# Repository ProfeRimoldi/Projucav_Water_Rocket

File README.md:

# 🚀 ProJuCAv – Water Rocket with Avionics

## 📡 Descripción del Proyecto

**ProJuCAv (Proyecto de Cohete de Agua con Aviónica)** es una iniciativa educativa basada en metodologías STEM que integra **física, electrónica, programación y diseño mecánico** en el desarrollo de un sistema aeroespacial a escala.

El proyecto propone el diseño, construcción y validación de un **cohete de agua instrumentado**, capaz de medir, registrar y transmitir datos de vuelo en tiempo real.

📘 Inspirado en programas aeroespaciales reales, el enfoque busca trasladar conceptos de ingeniería de alta complejidad a un entorno educativo práctico.

---

## 🎯 Objetivos

* Comprender los principios físicos de la **propulsión por reacción** (Tercera Ley de Newton) 
* Diseñar y construir un vehículo de lanzamiento funcional
* Desarrollar un sistema de **aviónica embarcada**
* Implementar una **estación terrena de telemetría**
* Analizar datos reales de vuelo
* Fomentar el trabajo colaborativo y multidisciplinario

📊 Según la planificación del proyecto, se estructura en etapas progresivas de diseño, integración y validación.

---

## 🧩 Arquitectura del Sistema

El sistema se divide en tres subsistemas principales:

### 🔧 Estructura (Mecánica)

* Botellas PET (fuselaje)
* Aletas aerodinámicas
* Sistema de presurización
* Plataforma de lanzamiento

### ⚡ Aviónica (Electrónica)

* Microcontrolador (ESP32)
* Sensores:

  * Altímetro barométrico (BMP280)
  * Acelerómetro (MPU6050)
* Sistema de almacenamiento local (microSD)
* Módulo de comunicación (LoRa)
* Sistema de alimentación (LiPo + regulación)

📌 La arquitectura electrónica completa se describe en 

---

### 📡 Estación Terrena

* Receptor de telemetría
* Computadora de procesamiento
* Software de visualización en tiempo real

---

## 📡 Telemetría y Adquisición de Datos

El sistema permite:

* Medición de **altura, aceleración y velocidad**
* Registro de datos en tiempo real y post-vuelo
* Transmisión inalámbrica a estación terrena

---

## 🚀 Propulsión

El cohete utiliza propulsión hidráulica basada en:

* Aire comprimido (energía potencial)
* Agua (masa de reacción)

✔ Basado en la **Tercera Ley de Newton**
✔ Expulsión de masa → generación de empuje

---

## 🪂 Sistema de Recuperación

El sistema de recuperación es crítico para la misión:

* Detección de apogeo mediante aviónica.
* Despliegue de paracaídas en apogeo.

---

## 🧪 Etapas del Proyecto

Según la planificación general:

1. **Diseño y fundamentos**
2. **Construcción del cohete**
3. **Integración de aviónica**
4. **Telemetría y pruebas**
5. **Lanzamiento final**

---

## 🛰️ Aviónica – Enfoque del Desarrollo

La aviónica evoluciona en niveles:

* 🔹 Nivel básico: sensores esenciales
* 🔹 Nivel intermedio: registro de datos (caja negra)
* 🔹 Nivel avanzado: telemetría en tiempo real
* 🔹 Nivel completo: sistema autónomo

---

## ⚙️ Tecnologías Utilizadas

* ESP32 (control principal)
* Sensores MEMS
* Comunicación inalámbrica

---

## 📁 Estructura del Repositorio

```bash
Projucav_Water_Rocket/
│
├── firmware/        # Código del sistema embebido
├── hardware/        # Diseño electrónico y PCB
├── docs/            # Documentación técnica y académica
└── README.md        # Descripción general del proyecto
```

---

## 👨‍🏫 Contexto Educativo

* Institución: Instituto Juan XXIII
* Modalidad: Aprendizaje basado en proyectos (PBL)
* Duración: ~5 meses
* Trabajo en equipos multidisciplinarios

---

## 🎓 Enfoque del Proyecto

Este proyecto busca replicar, a escala educativa, un sistema aeroespacial real, integrando:

* Ingeniería electrónica
* Física aplicada
* Programación embebida
* Diseño mecánico
* Análisis de datos

---

## 🚀 Autores / Desarrollo

**Diego Otero**; **Damián Rimoldi**
* Ingeniería en Electrónica – Docentes – Investigadores

Quien escribe:
Responsable del desarrollo de la **aviónica y sistema electrónico** del proyecto.

---

## 📌 Estado del Proyecto

🟡 En desarrollo
🔧 Etapa: Diseño e integración de sistemas

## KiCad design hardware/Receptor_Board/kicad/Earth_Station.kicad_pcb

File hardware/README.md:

Hardware Documentation.

Conexión de sensores: Usar firmware para detectar direcciones (ya cargado)
-MPU6050 (gyro) en bus I2C: DIR: 0x68
-BMP280 (Atmosferic Pressure) en bus I2C: Dir: 0x77

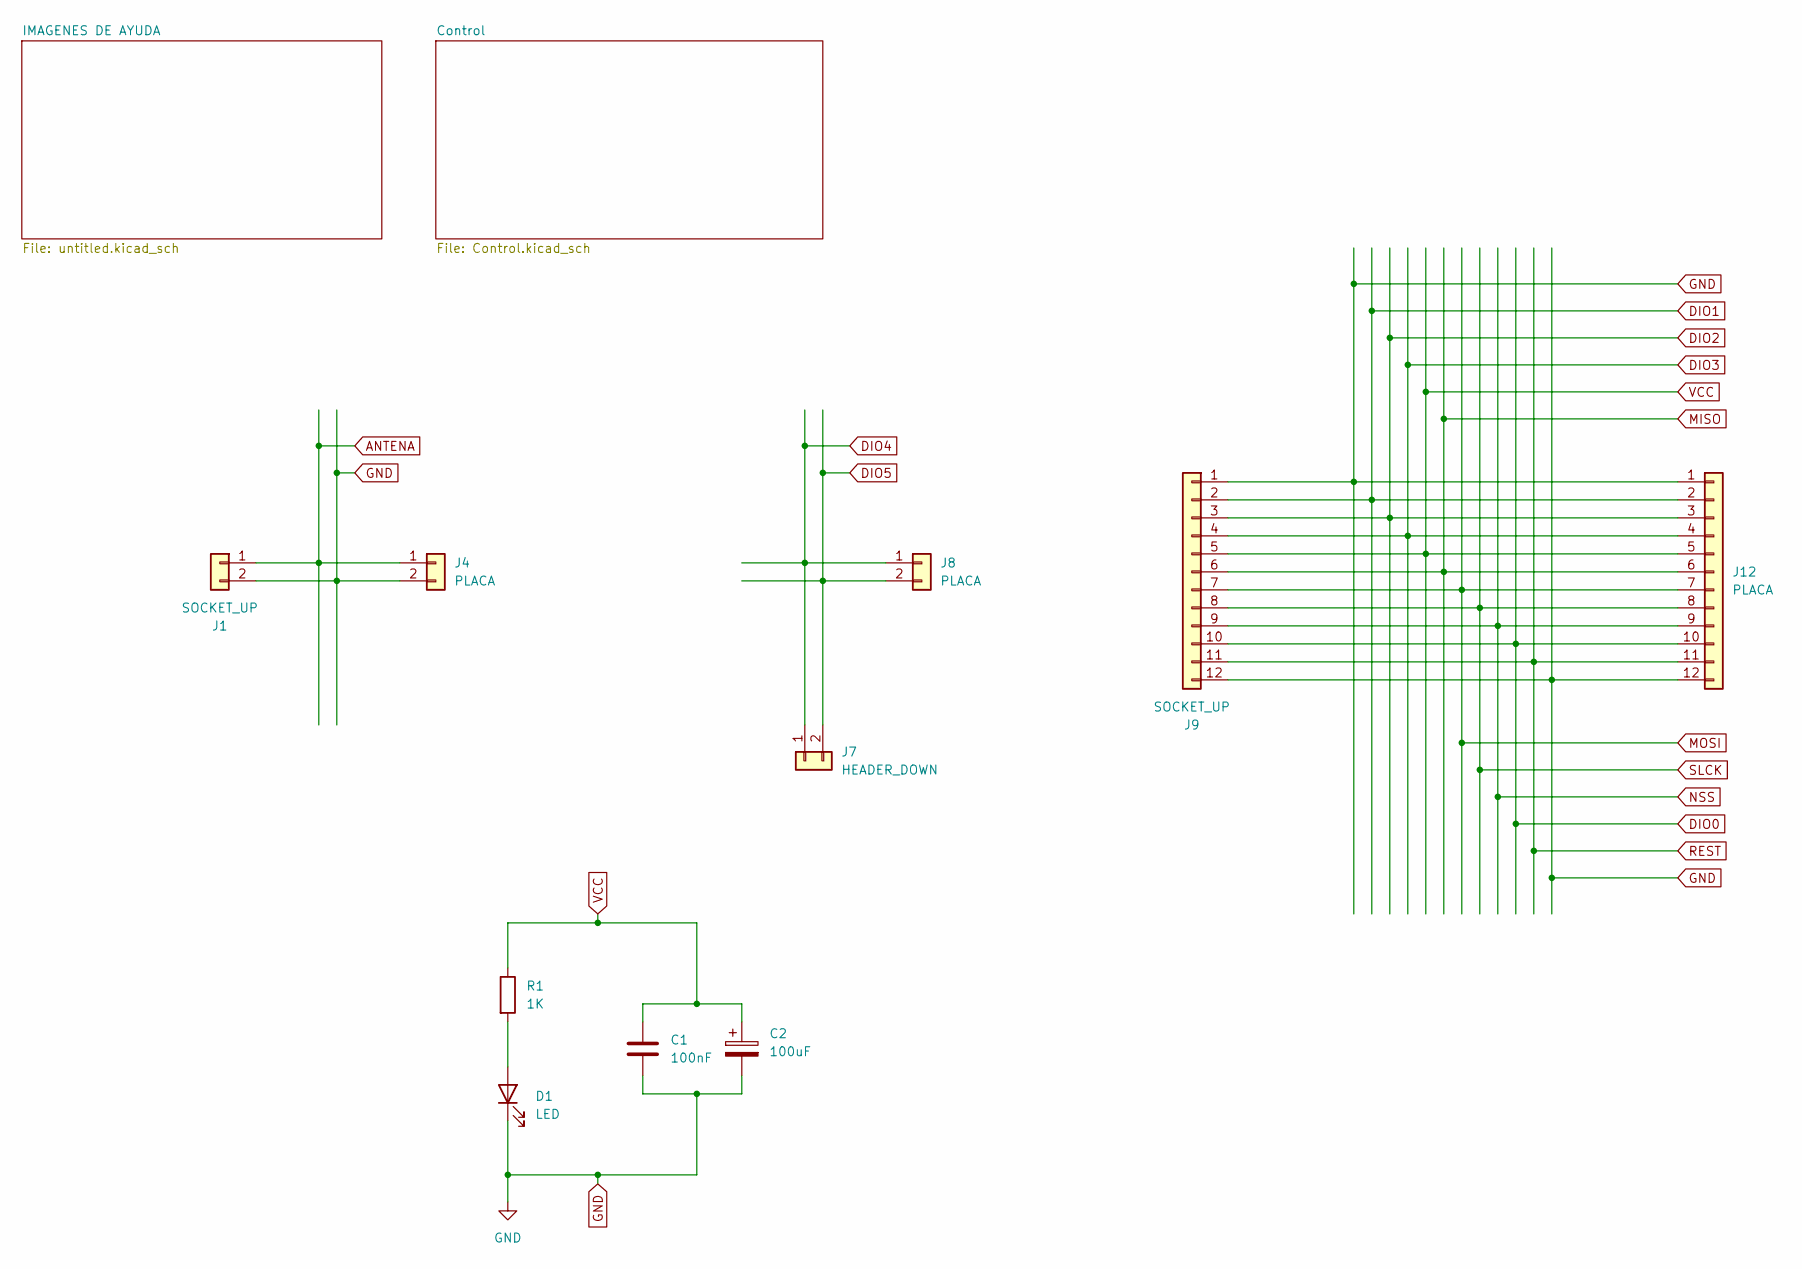
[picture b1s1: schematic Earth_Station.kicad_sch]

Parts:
C1: 100nF; C_0805_2012Metric
C2: 100uF; CP_Elec_5x3
D1: LED; LED_0805_2012Metric_Pad1.15x1.40mm_HandSolder
J1: SOCKET_UP; PinSocket_1x02_P2.54mm_Vertical
J4, J8: PLACA; PinHeader_1x02_P1.27mm_Vertical
J7: HEADER_DOWN; PinHeader_1x02_P2.54mm_Vertical
J9: SOCKET_UP; PinSocket_1x12_P2.54mm_Vertical
J12: PLACA; PinHeader_1x12_P1.27mm_Vertical
R1: 1K; R_0805_2012Metric_Pad1.20x1.40mm_HandSolder

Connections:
ANTENA: J1.1, J4.1
DIO0: J9.10, J12.10; also elsewhere on the board
DIO1: J9.2, J12.2
DIO2: J9.3, J12.3
DIO3: J9.4, J12.4
DIO4: J7.1, J8.1
DIO5: J7.2, J8.2
GND: C1.2, C2.2, D1.1 (K), J1.2, J4.2, J9.1, J9.12, J12.1, J12.12; also elsewhere on the board
MISO: J9.6, J12.6; also elsewhere on the board
MOSI: J9.7, J12.7; also elsewhere on the board
NSS: J9.9, J12.9; also elsewhere on the board
unnamed: D1.2 (A), R1.2
REST: J9.11, J12.11
SLCK: J9.8, J12.8; also elsewhere on the board
VCC: C1.1, C2.1, J9.5, J12.5, R1.1; also elsewhere on the board

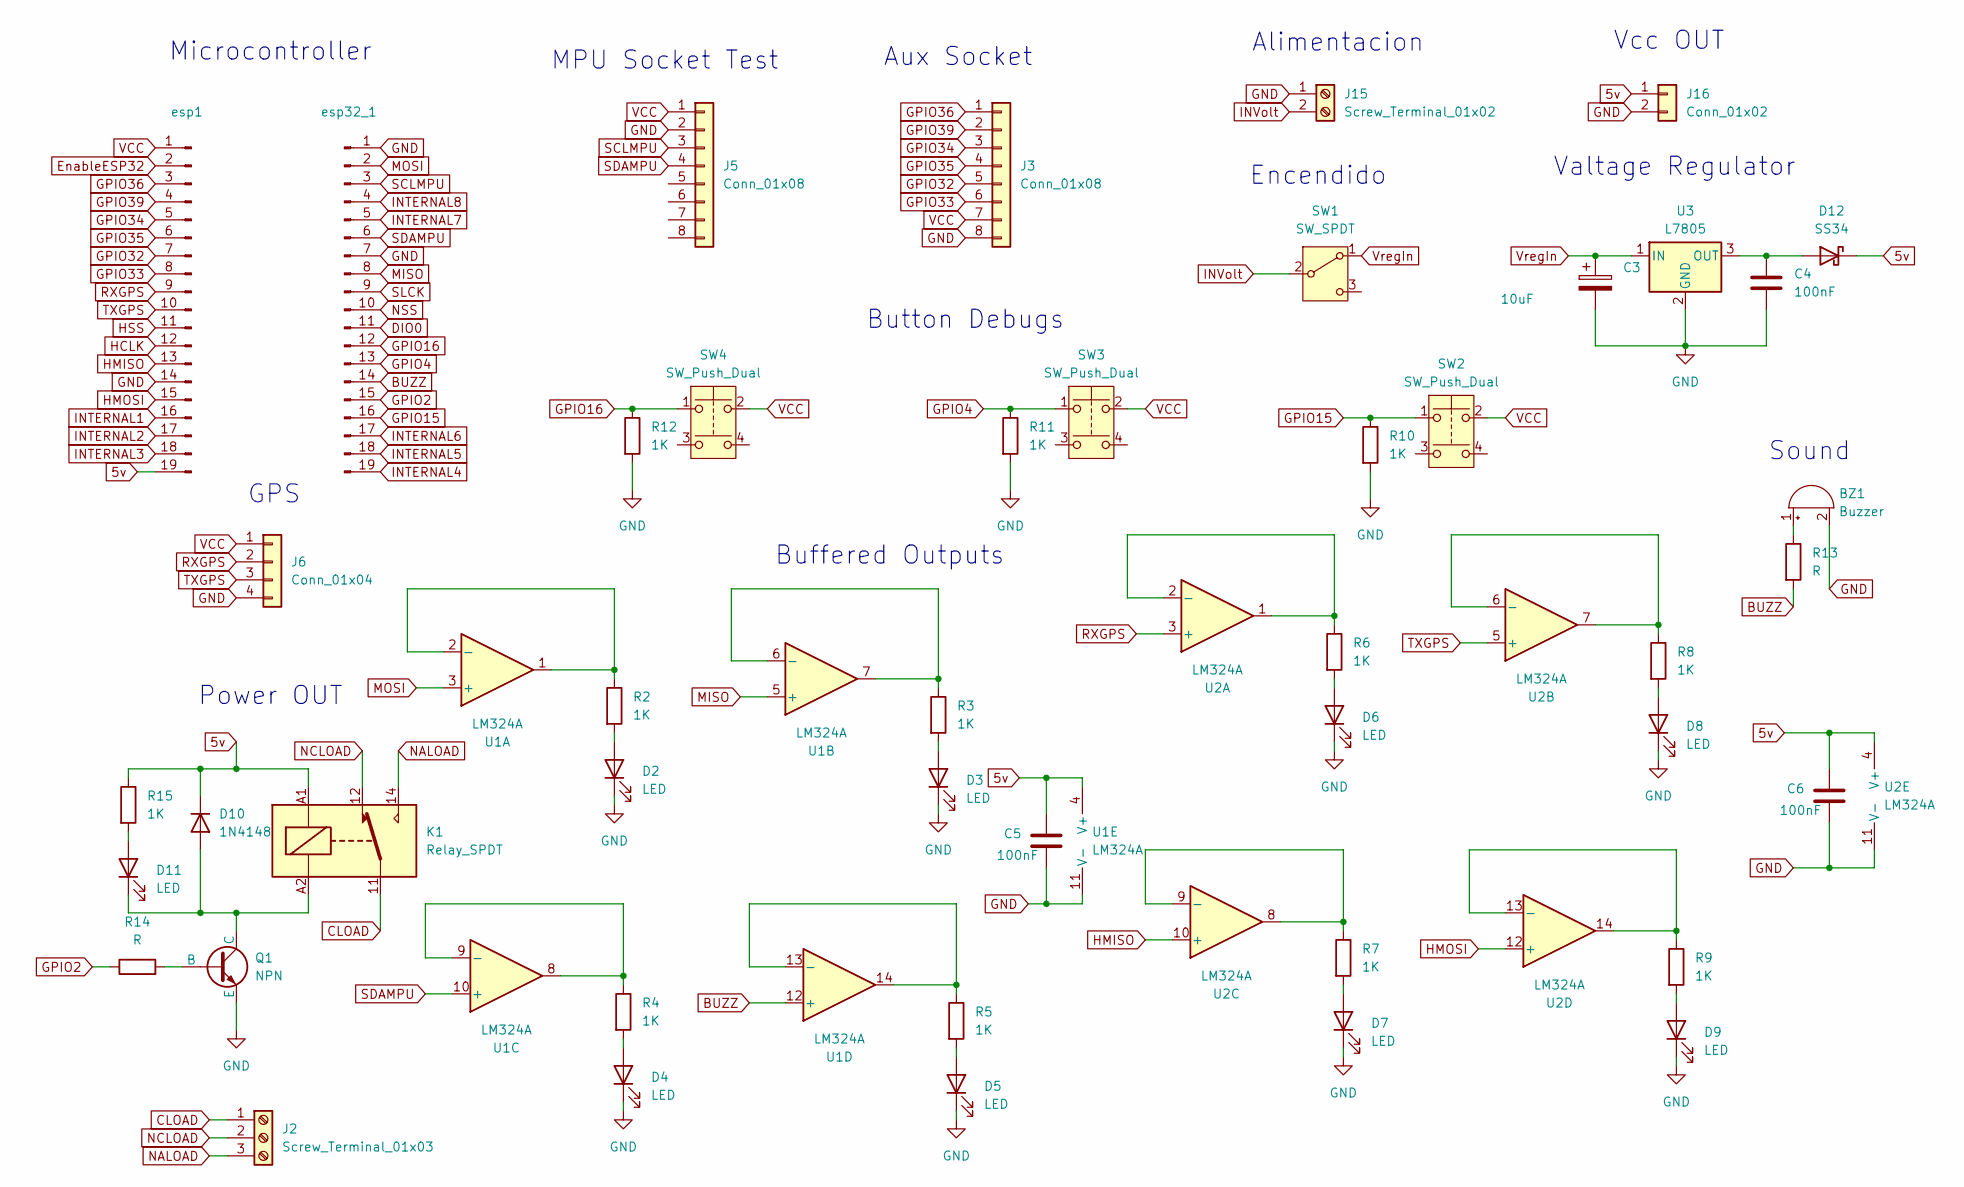
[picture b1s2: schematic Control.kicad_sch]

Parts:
BZ1: Buzzer; Buzzer_TDK_PS1240P02BT_D12.2mm_H6.5mm
C3: 10uF; CP_Elec_5x3.9
C4, C5, C6: 100nF; C_0805_2012Metric
D2, D3, D4, D5, D6, D7, D8, D9, D11: LED; LED_0805_2012Metric_Pad1.15x1.40mm_HandSolder
D10: 1N4148; D_DO-35_SOD27_P7.62mm_Horizontal
D12: SS34; D_3220_8050Metric_Pad2.65x5.15mm_HandSolder
J2: Screw_Terminal_01x03; TerminalBlock_bornier-3_P5.08mm
J3, J5: Conn_01x08; PinSocket_1x08_P2.54mm_Vertical
J6: Conn_01x04; PinSocket_1x04_P2.54mm_Vertical
J15: Screw_Terminal_01x02; TerminalBlock_bornier-2_P5.08mm
J16: Conn_01x02; PinSocket_1x02_P2.54mm_Vertical
K1: Relay_SPDT; Relay_SPDT_Finder_36.11
Q1: NPN; TO-92L_Inline
R2, R3, R4, R5, R6, R7, R8, R9, R10, R11, R12, R15: 1K; R_0805_2012Metric_Pad1.20x1.40mm_HandSolder
R13: R; R_0805_2012Metric_Pad1.20x1.40mm_HandSolder
R14: R; R_0805_2012Metric
SW1: SW_SPDT; SW_Slide_SPDT_Straight_CK_OS102011MS2Q
SW2, SW3, SW4: SW_Push_Dual; SW_Push_1P1T_NO_Vertical_Wuerth_434133025816
U1, U2: LM324A; SOIC-14_3.9x8.7mm_P1.27mm
U3: L7805; TO-263-2
esp1, esp32_1: Conn_01x19_Pin; PinSocket_1x19_P2.54mm_Vertical

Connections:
5v: C5.1, C6.1, D10.1 (K), D12.1 (K), J16.1, K1.A1, R15.1, U1.4 (V+), U2.4 (V+), esp1.19
BUZZ: R13.2, U1.12 (+), esp32_1.14
CLOAD: J2.1, K1.11
DIO0: esp32_1.11; also elsewhere on the board
EnableESP32: esp1.2
GND: BZ1.2 (-), C3.2, C4.2, C5.2, C6.2, D2.1 (K), D3.1 (K), D4.1 (K), D5.1 (K), D6.1 (K), D7.1 (K), D8.1 (K), D9.1 (K), J3.8, J5.2, J6.4, J15.1, J16.2, Q1.3 (E), R10.2, R11.2, R12.2, U1.11 (V-), U2.11 (V-), U3.2 (GND), esp1.14, esp32_1.1, esp32_1.7; also elsewhere on the board
GPIO2: R14.1, esp32_1.15
GPIO4: R11.1, SW3.1, esp32_1.13
GPIO15: R10.1, SW2.1, esp32_1.16
GPIO16: R12.1, SW4.1, esp32_1.12
GPIO32: J3.5, esp1.7
GPIO33: J3.6, esp1.8
GPIO34: J3.3, esp1.5
GPIO35: J3.4, esp1.6
GPIO36: J3.1, esp1.3
GPIO39: J3.2, esp1.4
HCLK: esp1.12
HMISO: U2.10 (+), esp1.13
HMOSI: U2.12 (+), esp1.15
HSS: esp1.11
INTERNAL1: esp1.16
INTERNAL2: esp1.17
INTERNAL3: esp1.18
INTERNAL4: esp32_1.19
INTERNAL5: esp32_1.18
INTERNAL6: esp32_1.17
INTERNAL7: esp32_1.5
INTERNAL8: esp32_1.4
INVolt: J15.2, SW1.2 (B)
MISO: U1.5 (+), esp32_1.8; also elsewhere on the board
MOSI: U1.3 (+), esp32_1.2; also elsewhere on the board
NALOAD: J2.3, K1.14
NCLOAD: J2.2, K1.12
NSS: esp32_1.10; also elsewhere on the board
unnamed: BZ1.1 (+), R13.1
unnamed: D2.2 (A), R2.2
unnamed: D3.2 (A), R3.2
unnamed: D4.2 (A), R4.2
unnamed: D5.2 (A), R5.2
unnamed: D6.2 (A), R6.2
unnamed: D7.2 (A), R7.2
unnamed: D8.2 (A), R8.2
unnamed: D9.2 (A), R9.2
unnamed: D10.2 (A), D11.1 (K), K1.A2, Q1.1 (C)
unnamed: D11.2 (A), R15.2
unnamed: C4.1, D12.2 (A), U3.3 (OUT)
unnamed: Q1.2 (B), R14.2
unnamed: R2.1, U1.1, U1.2 (-)
unnamed: R3.1, U1.6 (-), U1.7
unnamed: R4.1, U1.8, U1.9 (-)
unnamed: R5.1, U1.13 (-), U1.14
unnamed: R6.1, U2.1, U2.2 (-)
unnamed: R8.1, U2.6 (-), U2.7
unnamed: R7.1, U2.8, U2.9 (-)
unnamed: R9.1, U2.13 (-), U2.14
RXGPS: J6.2, U2.3 (+), esp1.9
SCLMPU: J5.3, esp32_1.3
SDAMPU: J5.4, U1.10 (+), esp32_1.6
SLCK: esp32_1.9; also elsewhere on the board
TXGPS: J6.3, U2.5 (+), esp1.10
VCC: J3.7, J5.1, J6.1, SW2.2, SW3.2, SW4.2, esp1.1; also elsewhere on the board
VregIn: C3.1, SW1.1 (A), U3.1 (IN)

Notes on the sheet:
Buffered Outputs
Microcontroller
GPS
Valtage Regulator
Vcc OUT
Encendido
Alimentacion
Aux Socket
MPU Socket Test
Button Debugs
Sound
Power OUT

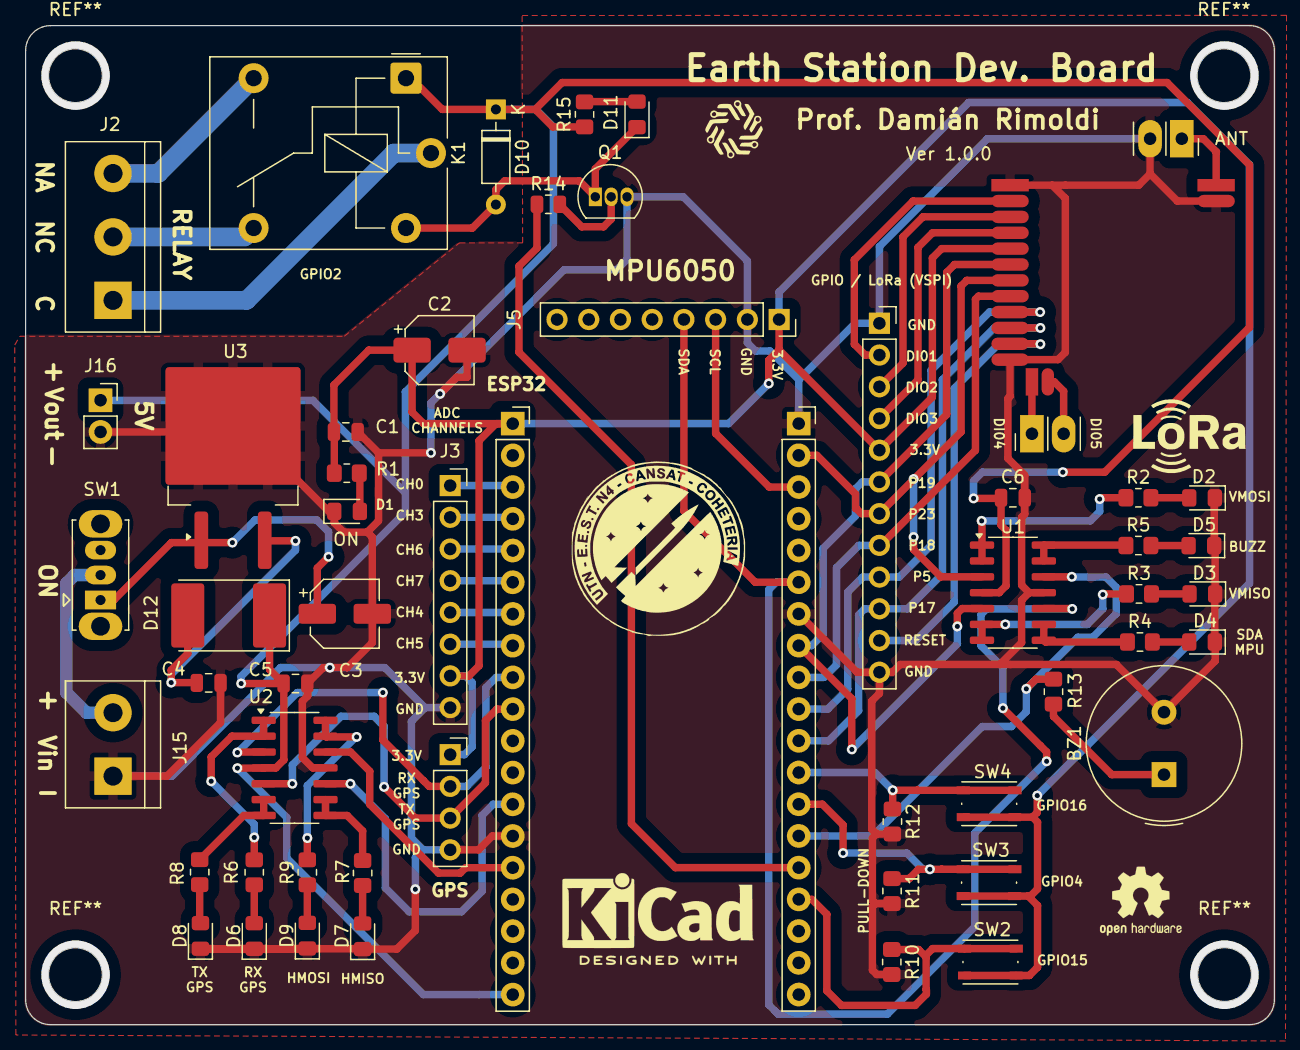
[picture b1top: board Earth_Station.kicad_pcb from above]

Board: 2 copper layers, 100.0 x 80.0 mm, 57 parts (0 on the bottom side), 59 nets.

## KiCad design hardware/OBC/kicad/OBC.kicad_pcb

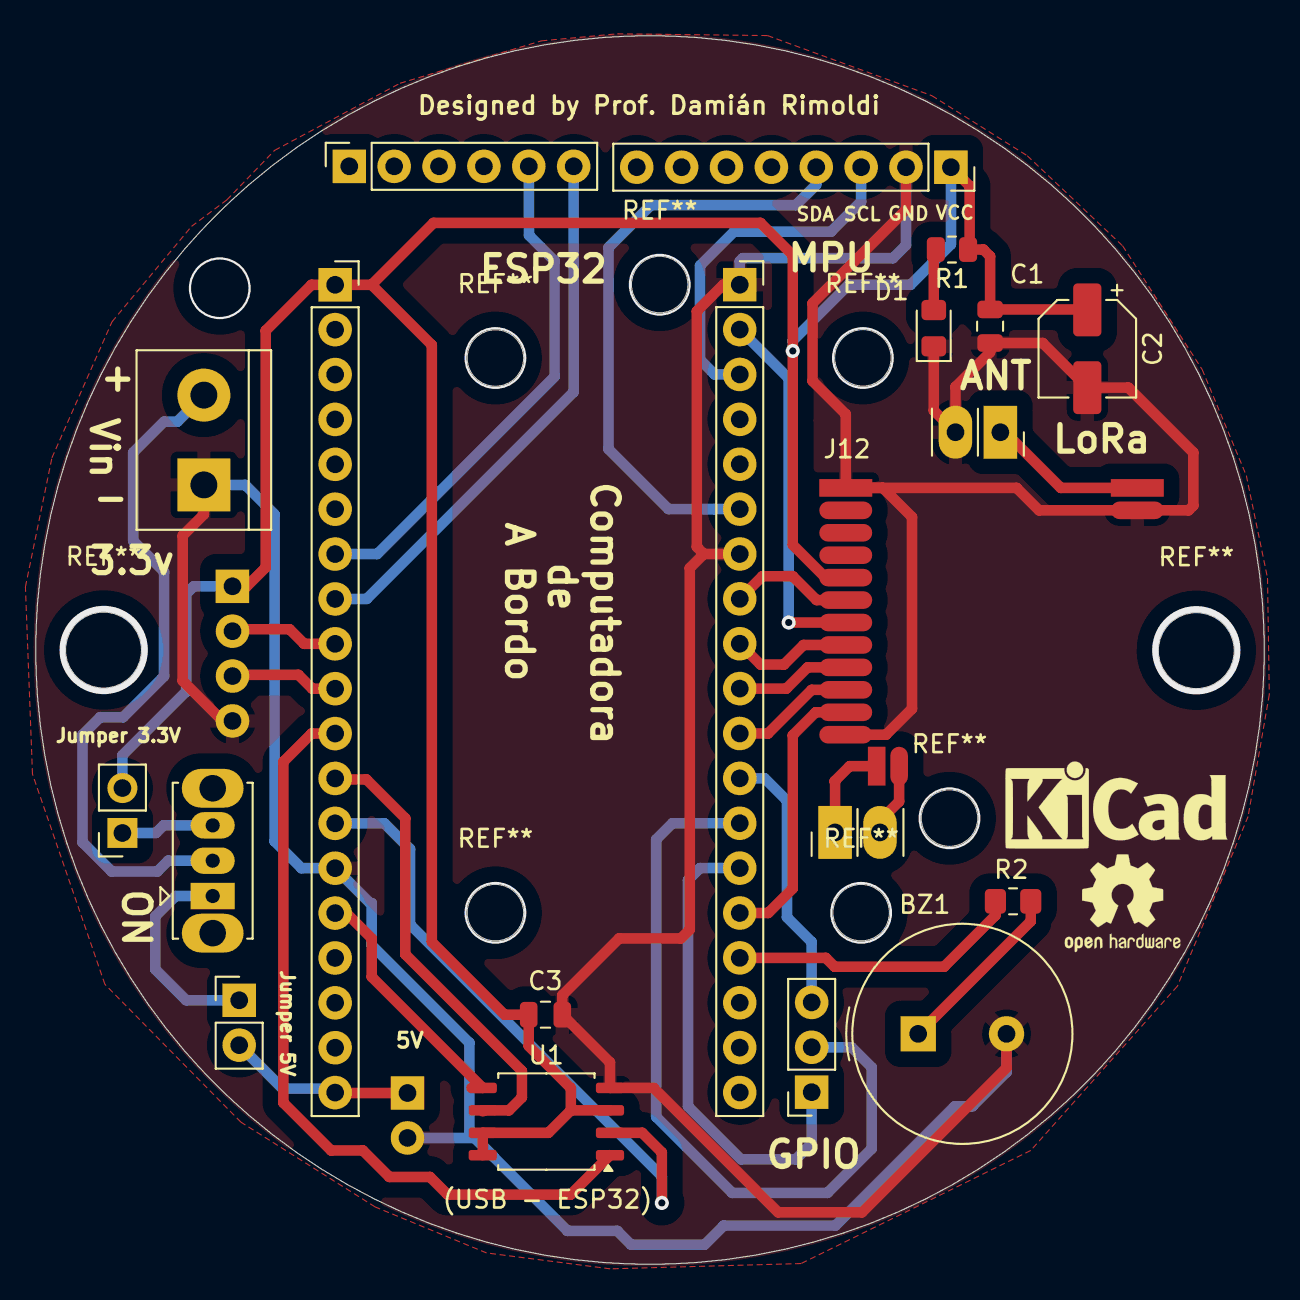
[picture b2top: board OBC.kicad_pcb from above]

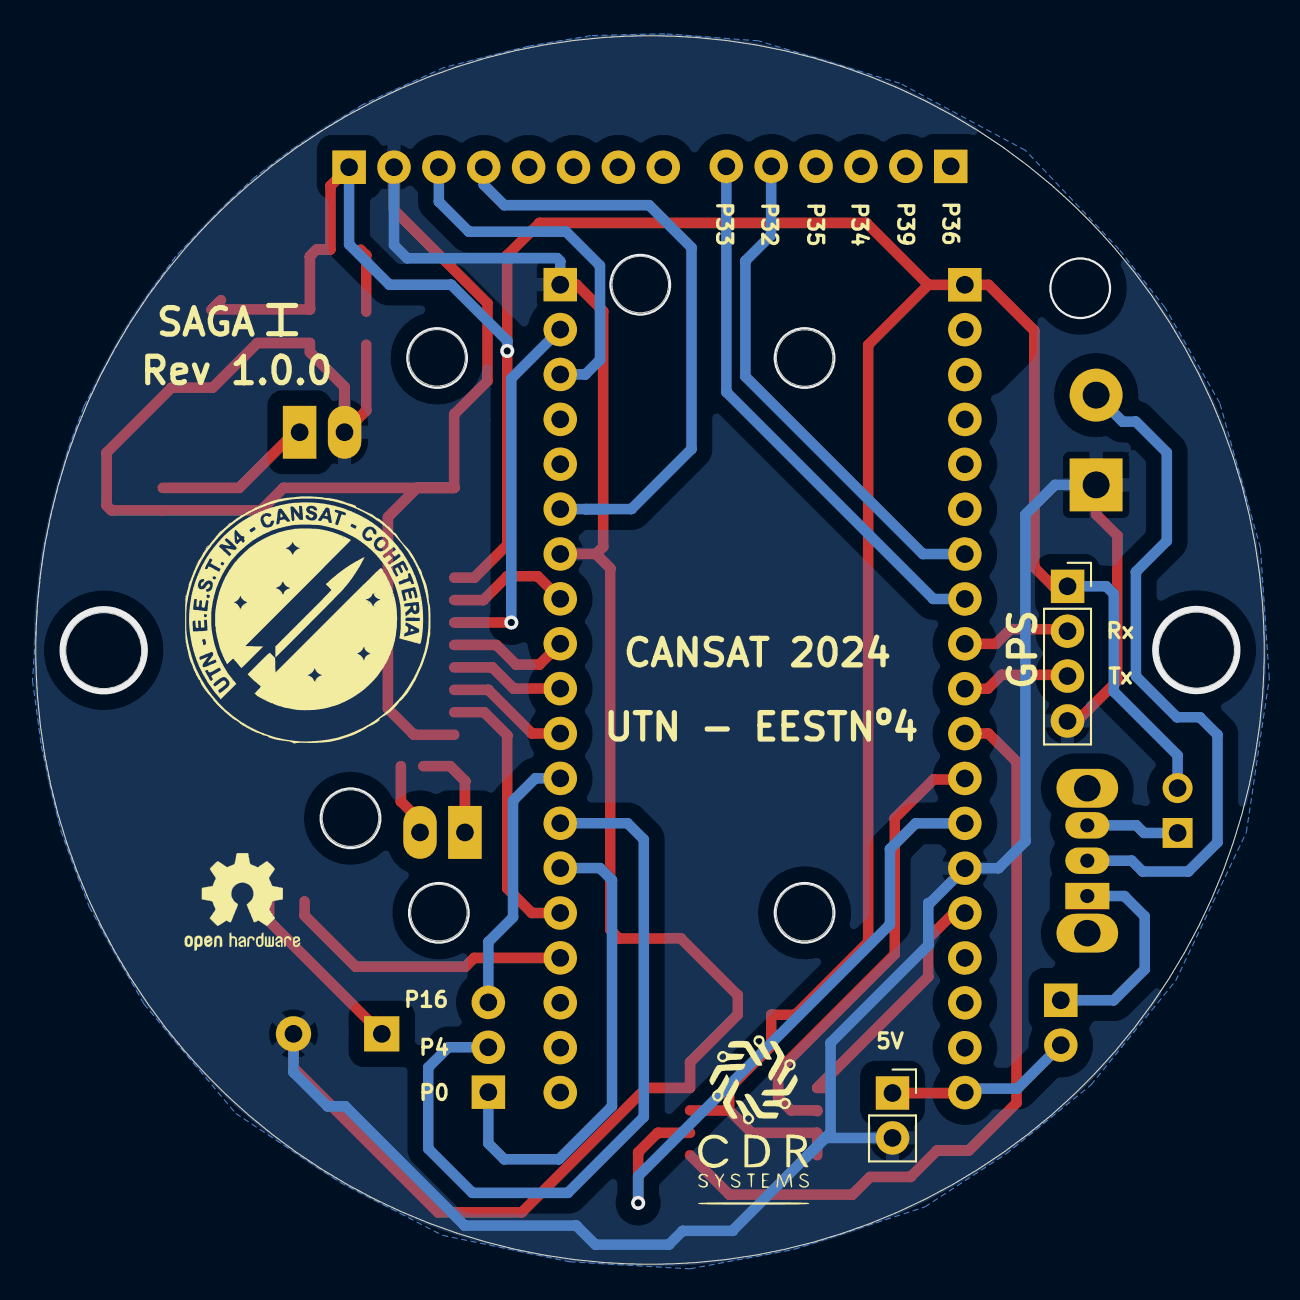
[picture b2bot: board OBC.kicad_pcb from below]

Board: 2 copper layers, 69.5 x 69.5 mm, 24 parts (2 on the bottom side), 35 nets.

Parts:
BZ1: Buzzer; Buzzer_TDK_PS1240P02BT_D12.2mm_H6.5mm
C1: 100nF; C_0805_2012Metric
C2: 100uF; CP_Elec_5x3.9
C3: C_Polarized_Small; C_0805_2012Metric
D1: LED; LED_0805_2012Metric_Pad1.15x1.40mm_HandSolder
J1: SOCKET_UP; PinSocket_1x02_P2.54mm_Vertical
J4, J8: PLACA; PinHeader_1x02_P1.27mm_Vertical
J7: HEADER_DOWN; PinHeader_1x02_P2.54mm_Vertical
J12: PLACA; PinHeader_1x12_P1.27mm_Vertical
J13: Conn_01x08_SocketMPU; PinSocket_1x08_P2.54mm_Vertical
J14: Conn_01x04_Socket; PinSocket_1x04_P2.54mm_Vertical
J15: Screw_Terminal_01x02; TerminalBlock_bornier-2_P5.08mm
J16, J21: Conn_01x02; PinSocket_1x02_P2.54mm_Vertical
J17: Conn_01x06_Socket; PinSocket_1x06_P2.54mm_Vertical
J18: Conn_01x02; PinHeader_1x02_P2.54mm_Vertical
J19: Conn_01x03; PinSocket_1x03_P2.54mm_Vertical
R1: 1K; R_0805_2012Metric
R2: R; R_0805_2012Metric_Pad1.20x1.40mm_HandSolder
SW1: SW_SPDT; SW_Slide_SPDT_Straight_CK_OS102011MS2Q
U1: 25CSM04xxSN; SOIC-8_5.23x5.23mm_P1.27mm
esp1, esp32_1: Conn_01x19_Pin; PinSocket_1x19_P2.54mm_Vertical

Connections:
5v: J16.1, J18.2, esp1.19
ANTENA: J1.1, J4.1
BUZZ: R2.2, esp32_1.16
DIO0: J12.10, esp32_1.11
DIO4: J7.1, J8.1
DIO5: J7.2, J8.2
GND: BZ1.2 (-), C1.2, C2.2, C3.2, D1.1 (K), J1.2, J4.2, J12.1, J12.12, J13.2, J14.4, J15.1, J16.2, U1.4 (V_{SS}), esp1.14, esp32_1.1, esp32_1.7
GPIO0: J19.1, esp32_1.14
GPIO4: J19.2, esp32_1.13
GPIO16: J19.3, esp32_1.12
GPIO32: J17.5, esp1.7
GPIO33: J17.6, esp1.8
GPIO34: J17.3, esp1.5
GPIO35: J17.4, esp1.6
GPIO36: J17.1, esp1.3
GPIO39: J17.2, esp1.4
HCLK: U1.6 (SCK), esp1.12
HMISO: U1.2 (SO), esp1.13
HMOSI: U1.5 (SI), esp1.15
HSS: U1.1 (~CS), esp1.11
INVolt: J15.2, SW1.2 (B)
MISO: J12.6, esp32_1.8
MOSI: J12.7, esp32_1.2
NSS: J12.9, esp32_1.10
unnamed: BZ1.1 (+), R2.1
unnamed: D1.2 (A), R1.2
Pup: J18.1, SW1.1 (A)
REST: J12.11, esp32_1.15
RXGPS: J14.2, esp1.9
SCLMPU: J13.3, esp32_1.3
SDAMPU: J13.4, esp32_1.6
SLCK: J12.8, esp32_1.9
TXGPS: J14.3, esp1.10
VCC: C1.1, C2.1, C3.1, J12.5, J13.1, J14.1, J21.2, R1.1, U1.3 (~WP), U1.7 (~HOLD), U1.8 (V_{CC}), esp1.1
VCC1: J21.1, SW1.3 (C)

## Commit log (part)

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2026-05-03 Initial README file
2026-05-03 Fix general README.md file
2026-05-03 Initialize branch directory projetc
2026-05-03 Incorporated Receptor Board
2026-05-04 Add files: On Board Computer
2026-05-04 Adapt Barometric Pressure Sensor in J17 connector socket
2026-05-04 Organize General Structure for Hardware
2026-05-05 First actualization for OBC PCB
2026-05-05 Add docs for entregas
2026-05-10 Add firmware Test and documentation Firmware and Hardwarefor mods
2026-05-11 Add To-Do List in README.md general file, from specification of Servo-motor Connection, and add text in Hardware OBC schematic file.
2026-06-01 Actualizo archivos de firmware y archivos README.md de Hardware y Firmware
2026-06-01 Agrego firmware de simulacion de despegue y apogeo
2026-06-01 Agrego archivo README.md de documentacion de codigo de simulacion
2026-06-17 Fix bug on initialization of LoRa module
2026-06-17 Add new readme.md
2026-06-17 Add final firmware for test Completo_V1.ino
